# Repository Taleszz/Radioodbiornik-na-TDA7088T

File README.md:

# Radioodbiornik-na-TDA7088T
Radioodbiornik FM oparty na układzie scalonym TDA7088T. Współautorem projektu jest Mateusz Polek

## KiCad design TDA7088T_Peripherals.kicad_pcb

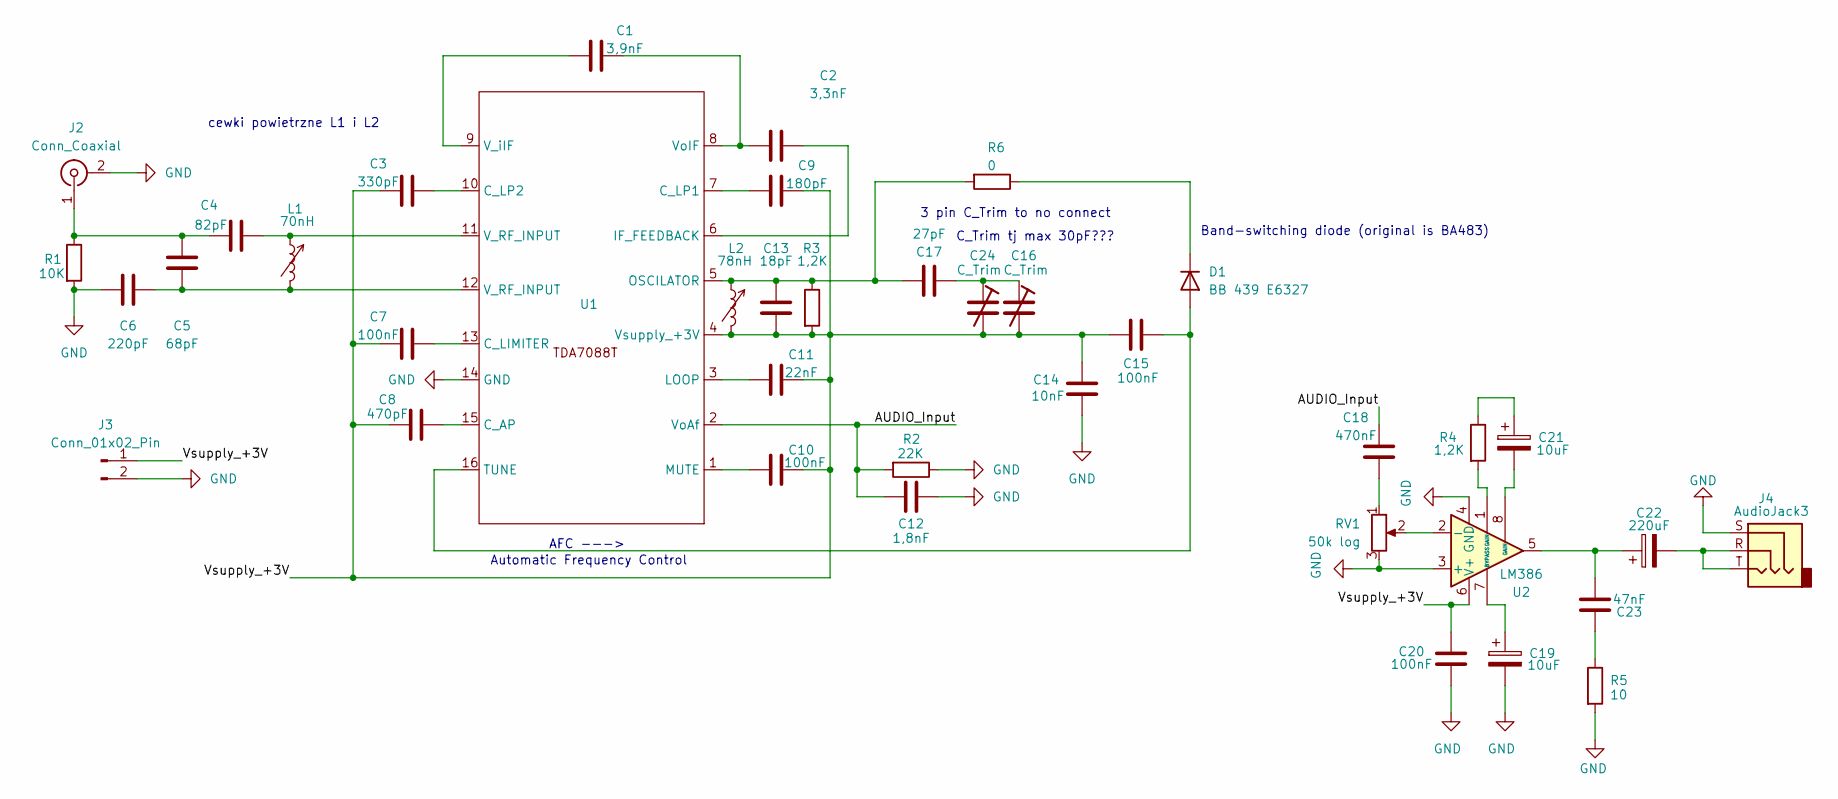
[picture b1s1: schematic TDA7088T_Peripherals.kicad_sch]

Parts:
C1: 3,9nF; C_0805_2012Metric_Pad1.18x1.45mm_HandSolder
C2: 3,3nF; C_0805_2012Metric_Pad1.18x1.45mm_HandSolder
C3: 330pF; C_0805_2012Metric_Pad1.18x1.45mm_HandSolder
C4: 82pF; C_0805_2012Metric_Pad1.18x1.45mm_HandSolder
C5: 68pF; C_0805_2012Metric_Pad1.18x1.45mm_HandSolder
C6: 220pF; C_0805_2012Metric_Pad1.18x1.45mm_HandSolder
C7, C10, C15, C20: 100nF; C_0805_2012Metric_Pad1.18x1.45mm_HandSolder
C8: 470pF; C_0805_2012Metric_Pad1.18x1.45mm_HandSolder
C9: 180pF; C_0805_2012Metric_Pad1.18x1.45mm_HandSolder
C11: 22nF; C_0805_2012Metric_Pad1.18x1.45mm_HandSolder
C12: 1,8nF; C_0805_2012Metric_Pad1.18x1.45mm_HandSolder
C13: 18pF; C_0805_2012Metric_Pad1.18x1.45mm_HandSolder
C14: 10nF; C_0805_2012Metric_Pad1.18x1.45mm_HandSolder
C16, C24: C_Trim; variable capacitor 90deg 3 leg
C17: 27pF; C_0805_2012Metric_Pad1.18x1.45mm_HandSolder
C18: 470nF; C_0805_2012Metric_Pad1.18x1.45mm_HandSolder
C19, C21: 10uF; CP_Radial_D5.0mm_P2.00mm
C22: 220uF; CP_Radial_D6.3mm_P2.50mm
C23: 47nF; C_0805_2012Metric_Pad1.18x1.45mm_HandSolder
D1: BB 439 E6327; D_SOD-323_HandSoldering
J2: Conn_Coaxial; SMA_Amphenol_132134_Vertical
J3: Conn_01x02_Pin; Molex_KK-396_5273-02A_1x02_P3.96mm_Vertical
J4: AudioJack3; Jack_3.5mm_CUI_SJ-3523-SMT_Horizontal
L1: 70nH; JLC05E088TRVSM
L2: 78nH; JLC05E088TRVSM
R1: 10K; R_0805_2012Metric_Pad1.20x1.40mm_HandSolder
R2: 22K; R_0805_2012Metric_Pad1.20x1.40mm_HandSolder
R3, R4: 1,2K; R_0805_2012Metric_Pad1.20x1.40mm_HandSolder
R5: 10; R_0805_2012Metric_Pad1.20x1.40mm_HandSolder
R6: 0; R_0402_1005Metric_Pad0.72x0.64mm_HandSolder
RV1: 50k log; Potentiometer_Vishay_TS53YL_Vertical
U1: SOIC-16_3.9x9.9mm_P1.27mm
U2: LM386; SOIC-8_3.9x4.9mm_P1.27mm

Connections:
/AUDIO_Input: C12.1, C18.1, R2.2, U1.2 (VoAf)
/Vsupply_+3V: C3.1, C7.1, C8.1, C9.1, C10.2, C11.2, C13.1, C14.2, C15.2, C16.2, C20.1, C24.2, J3.1, L2.2, R3.2, U1.4 (Vsupply_+3V), U2.6 (V+)
GND: C6.2, C12.2, C14.1, C19.2, C20.2, J2.2 (Ext), J3.2, J4.S, R1.2, R2.1, R5.2, RV1.3, U1.14 (GND), U2.3 (+), U2.4 (GND)
unnamed: C4.2, L1.1, U1.11 (V_RF_INPUT)
unnamed: C5.1, C6.1, L1.2, U1.12 (V_RF_INPUT)
unnamed: C16.1, C17.1, C24.1
unnamed: C18.2, RV1.1
unnamed: C21.1, R4.1
unnamed: C21.2, U2.8 (GAIN)
unnamed: C22.1, C23.1, U2.5
unnamed: C22.2, J4.R, J4.T
unnamed: C23.2, R5.1
unnamed: C15.1, D1.2 (A), U1.16 (TUNE)
unnamed: D1.1 (K), R6.1
unnamed: C4.1, C5.2, J2.1 (In), R1.1
unnamed: R4.2, U2.1 (GAIN)
unnamed: C8.2, U1.15 (C_AP)
unnamed: C7.2, U1.13 (C_LIMITER)
unnamed: C9.2, U1.7 (C_LP1)
unnamed: C3.2, U1.10 (C_LP2)
unnamed: C2.1, U1.6 (IF_FEEDBACK)
unnamed: C11.1, U1.3 (LOOP)
unnamed: C10.1, U1.1 (MUTE)
unnamed: C13.2, C17.2, L2.1, R3.1, R6.2, U1.5 (OSCILATOR)
unnamed: C1.1, U1.9 (V_iIF)
unnamed: C1.2, C2.2, U1.8 (VoIF)
unnamed: RV1.2, U2.2 (-)
unnamed: C19.1, U2.7 (BYPASS)

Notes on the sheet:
3 pin C_Trim to no connect
Automatic Frequency Control
Band-switching diode (original is BA483)
C_Trim tj max 30pF???
AFC --->
cewki powietrzne L1 i L2

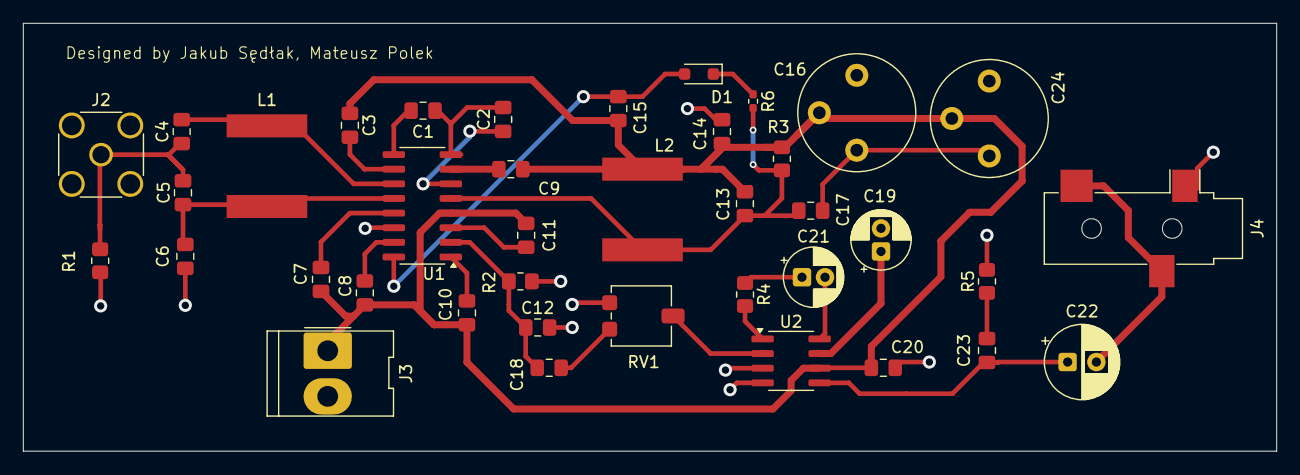
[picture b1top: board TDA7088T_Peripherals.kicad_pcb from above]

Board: 2 copper layers, 108.8 x 37.1 mm, 39 parts (0 on the bottom side), 28 nets.

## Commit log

2025-12-26 Uploaded the project to the web
    A project that was developed locally has now been successfully published and made accessible on the web.
